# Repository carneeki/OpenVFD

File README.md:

# OpenVFD
Variable Frequency Drive for ATmega328 based Arduinos

A variable frequency drive is a method for controlling AC motors, typically used
in machinery such as a drill press, milling machine or lathe. A VFD typically
permits the use of running 3 phase motors on single phase power, and running
single phase motors on 3 phase power.

The Arduino code presented here will produce 3 PWM signals that approximate sine
waves suitable to drive some transistors that can be used to power AC motors.

EAGLE schematics will later pop up with potential (but untested) circuits that
can be used connect machinery.

VFDs follow several stages, and can be broken up into 3 separate circuits:

1. AC->DC rectification. This means that AC coming in is turned into DC power.
DC power is smoothed out for fewer ripples. This is where 3 phase really shines, there's a lot less ripple.
1. DC->AC inverter. Gnomes receive signals from a controller to turn a bunch of
switches on and off really fast so the motor thinks it sees AC power. Depending
on how fast the gnomes are clicking the switches controls how fast the motor
spins.
1. The controller is the final circuit, which the Arduino code concerns itself
with.

## AC->DC rectification
For single phase circuits, a standard bridge rectifier can be used.
For three phase circuits, a 3 phase rectifier is required (can be made from 6 diodes).

Once DC comes in, a smoothing capacitor (or a bank of them) is required. The
size of the caps depends on the power in and power out.

## DC->AC inverter
The gnomes mentioned are actually MOSFETs, a type of transistor. 6 of them are
hooked up with 3 in parallel from +DC to one leg of each motor. The other three
are connected from each leg of the motor to GND. The gate (or signal receiver)
needs to be hooked up correctly to the controller.

## Inverter Controller
This circuit consists of an Arduino producing three PWM sine waves that go
through a low pass filter. The low pass filter then goes into a device called a comparator. When the sine wave is high, one pin is turned on and goes to the
MOSFET connected to +DC and motor, the other pin is turned off which goes to
the MOSFET connected to the motor and GND.

Certain MOSFETs have trouble remaining on when high voltages are pushed through
them, so it may be necessary to use a controller chip that prevents certain
dangerous conditions, as well as providing an idea of how much juice the motor
is drawing.

## Thanks and references
Much of this code is very very similar to the works found at CPSU and AMAC
below, but with more comments, and designed for use in driving motors.

Omar David Munoz, senior project,
California Polytechnic State University
http://digitalcommons.calpoly.edu/cgi/viewcontent.cgi?article=1129&context=eesp

Martin Nawrath, "Arduino DDS Sine Wave Generator",
Academy of Media Arts Cologne
http://interface.khm.de/index.php/lab/interfaces-advanced/arduino-dds-sinewave-generator/

And the datasheet which is referenced quite a lot in OpenVFD.ino
http://www.atmel.com/images/Atmel-8271-8-bit-AVR-Microcontroller-ATmega48A-48PA-88A-88PA-168A-168PA-328-328P_datasheet_Complete.pdf

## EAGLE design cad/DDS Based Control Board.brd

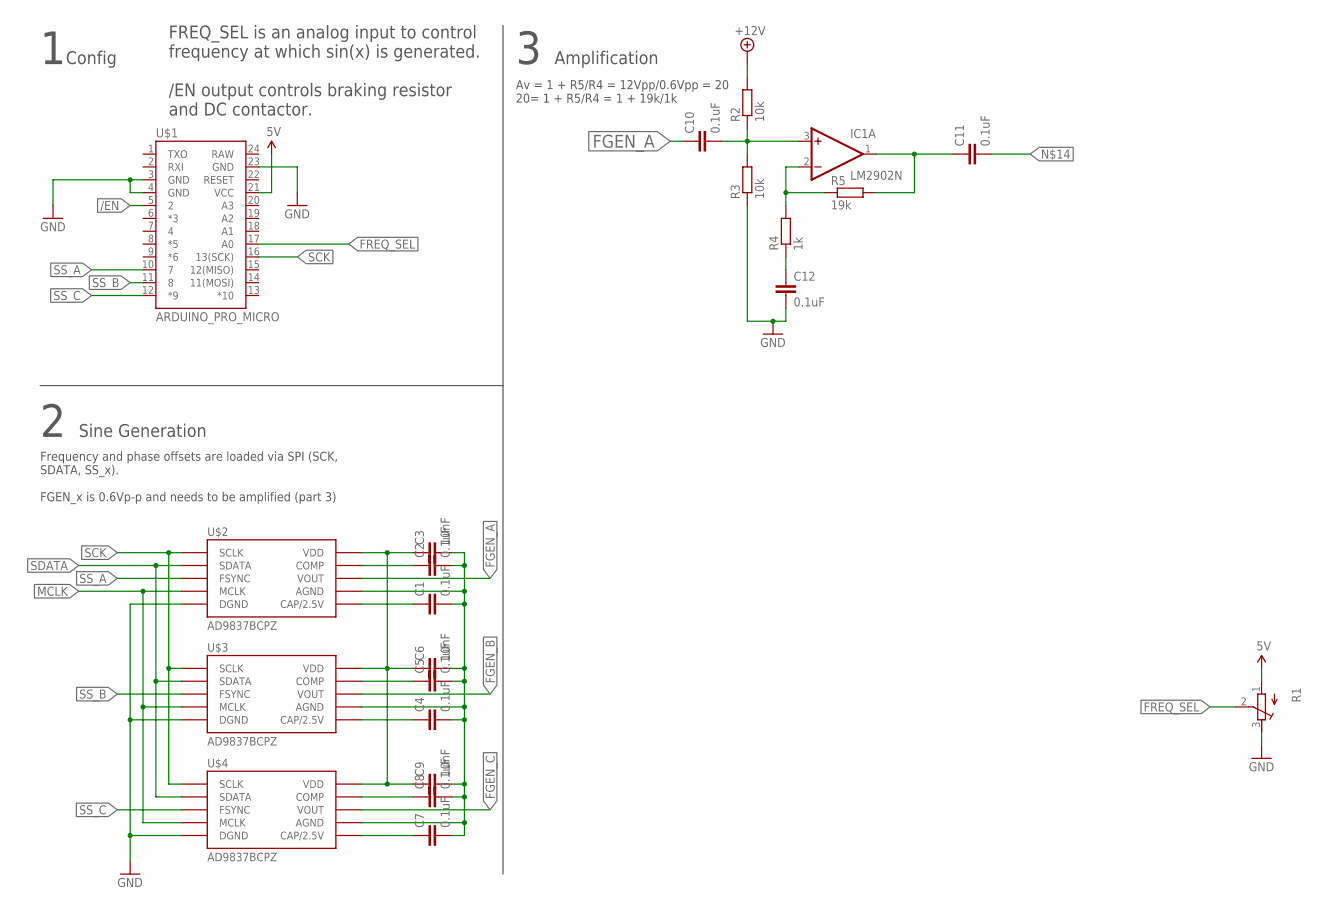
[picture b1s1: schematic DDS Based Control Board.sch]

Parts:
C1, C2, C4, C5, C7, C8, C10, C11, C12: 0.1uF; C025-025X050
C3, C6, C9: 10nF; C025-025X050
IC1: LM2902N; DIL14
R1: R-TRIMM64X; RTRIM64X
R2, R3: 10k; 0207/7
R4: 1k; 0207/7
R5: 19k; 0207/7
U$1: ARDUINO_PRO_MICRO
U$2, U$3, U$4: AD9837BCPZ; AD9837

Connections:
5V: R1.1 (A)
+12V: R2.2
/EN: U$1.5 (2)
FGEN_A: C10.1, U$2.P$10 (VOUT)
FGEN_B: U$3.P$10 (VOUT)
FGEN_C: U$4.P$10 (VOUT)
FREQ_SEL: R1.2 (S), U$1.17 (A0)
GND: C12.2, R1.3 (E), R3.1, U$1.3 (GND), U$1.4 (GND), U$1.23 (GND)
MCLK: U$2.P$5 (MCLK), U$3.P$5 (MCLK), U$4.P$5 (MCLK)
unnamed: C3.1, C6.1, C9.1, U$2.P$2 (VDD), U$3.P$2 (VDD), U$4.P$2 (VDD)
unnamed: C1.2, C2.2, C3.2, C4.2, C5.2, C6.2, C7.2, C8.2, C9.2, U$2.P$9 (AGND), U$3.P$9 (AGND), U$4.P$9 (AGND)
unnamed: C1.1, U$2.P$3 (CAP/2.5V)
unnamed: U$2.P$0 (DGND), U$2.P$4 (DGND), U$3.P$0 (DGND), U$3.P$4 (DGND), U$4.P$0 (DGND), U$4.P$4 (DGND)
unnamed: C2.1, U$2.P$1 (COMP)
unnamed: C5.1, U$3.P$1 (COMP)
unnamed: C8.1, U$4.P$1 (COMP)
unnamed: C7.1, U$4.P$3 (CAP/2.5V)
unnamed: C4.1, U$3.P$3 (CAP/2.5V)
unnamed: C10.2, IC1.3 (+IN), R2.1, R3.2
unnamed: C11.1, IC1.1 (OUT), R5.2
unnamed: IC1.2 (-IN), R4.2, R5.1
unnamed: C12.1, R4.1
SCK: U$1.16 (13(SCK)), U$2.P$7 (SCLK), U$3.P$7 (SCLK), U$4.P$7 (SCLK)
SDATA: U$2.P$6 (SDATA), U$3.P$6 (SDATA), U$4.P$6 (SDATA)
SS_A: U$1.10 (7), U$2.P$8 (FSYNC)
SS_B: U$1.11 (8), U$3.P$8 (FSYNC)
SS_C: U$1.12 (*9), U$4.P$8 (FSYNC)
V+: IC1.4 (V+)
V-: IC1.11 (V-)
VCC: U$1.21 (VCC)

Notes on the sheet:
FREQ_SEL is an analog input to control frequency at which sin(x) is generated. /EN output controls braking resistor and DC contactor.
Frequency and phase offsets are loaded via SPI (SCK, SDATA, SS_x). FGEN_x is 0.6Vp-p and needs to be amplified (part 3)
Config
Sine Generation
Amplification
Av = 1 + R5/R4 = 12Vpp/0.6Vpp = 20 20= 1 + R5/R4 = 1 + 19k/1k

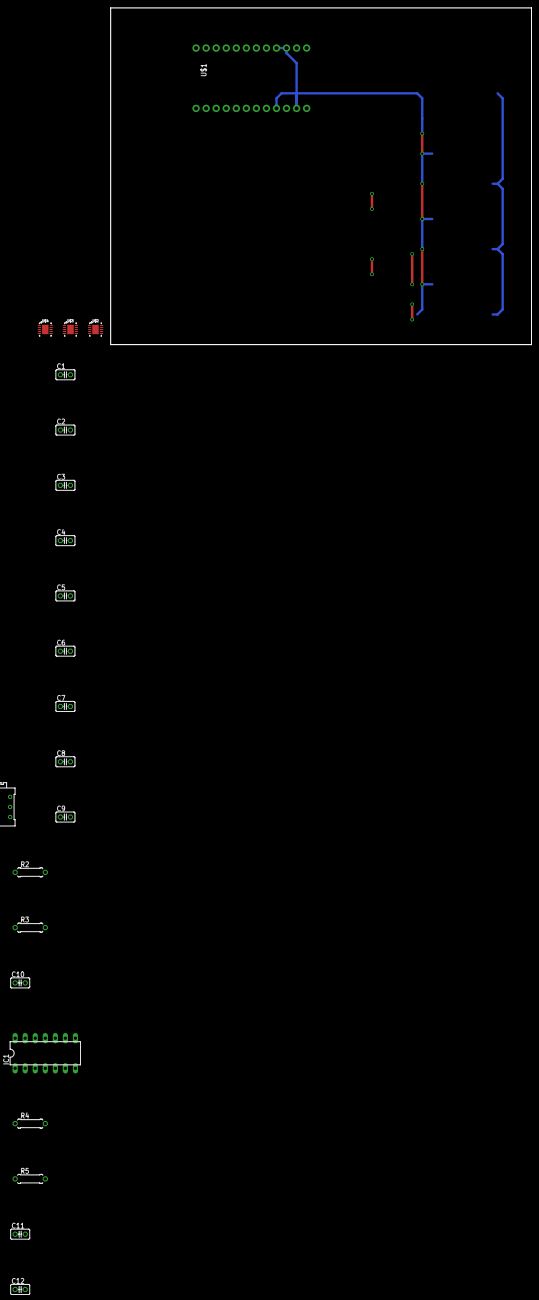
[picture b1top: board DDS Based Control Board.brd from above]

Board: 2 copper layers, 106.3 x 85.1 mm, 22 parts (0 on the bottom side), 22 nets.

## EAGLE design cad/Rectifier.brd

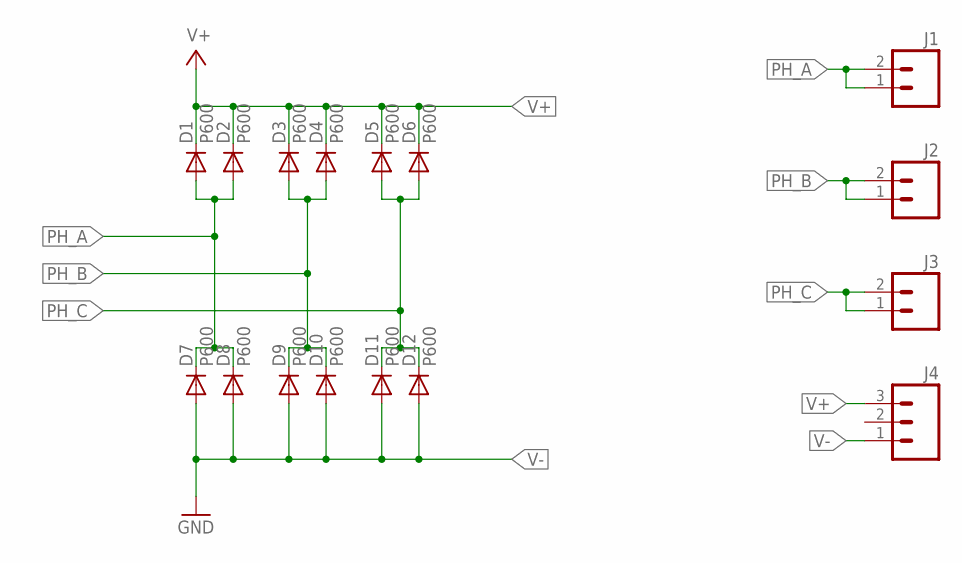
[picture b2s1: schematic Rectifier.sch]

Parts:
D1, D2, D3, D4, D5, D6, D7, D8, D9, D10, D11, D12: P600; P6-15
J1, J2, J3: M025MM; SCREWTERMINAL-5MM-2
J4: M03-SCREW-5MM; SCREWTERMINAL-5MM-3

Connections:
PH_A: D1.A, D2.A, D7.C, D8.C, J1.1, J1.2
PH_B: D3.A, D4.A, D9.C, D10.C, J2.1, J2.2
PH_C: D5.A, D6.A, D11.C, D12.C, J3.1, J3.2
V+: D1.C, D2.C, D3.C, D4.C, D5.C, D6.C, J4.3
V-: D7.A, D8.A, D9.A, D10.A, D11.A, D12.A, J4.1

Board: 2 copper layers, 16 parts (0 on the bottom side), 5 nets, no tracks yet.

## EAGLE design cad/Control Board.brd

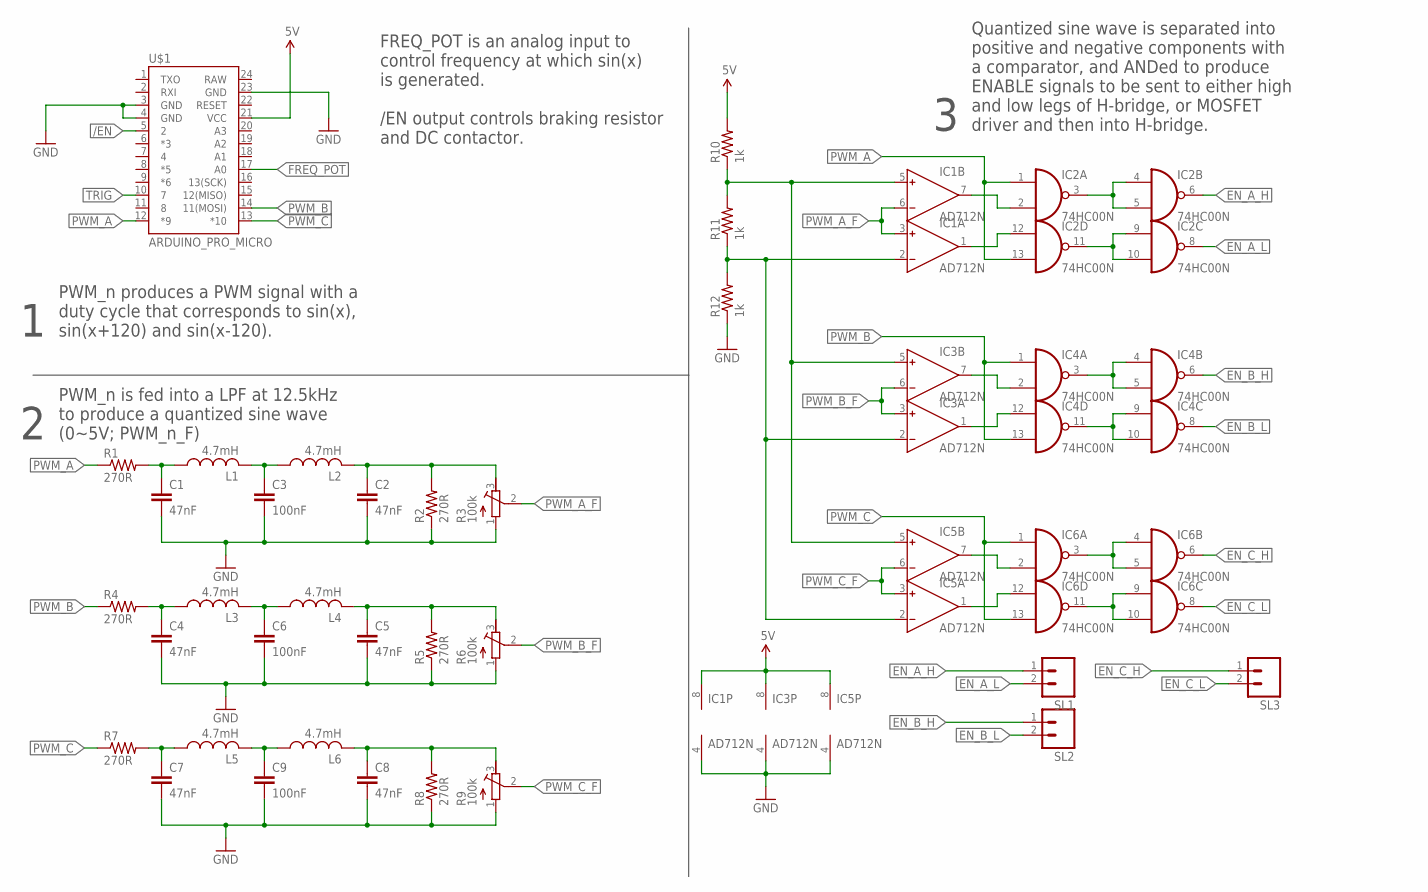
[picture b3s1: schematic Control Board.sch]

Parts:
C1, C2, C4, C5, C7, C8: 47nF; C025-025X050
C3, C6, C9: 100nF; C025-025X050
IC1, IC3, IC5: AD712N; DIL08
IC2, IC4, IC6: 74HC00N; DIL14
L1, L2, L3, L4, L5, L6: 4.7mH; 0207/12
R1, R2, R4, R5, R7, R8: 270R; 0207/7
R3, R6, R9: 100k; RTRIM3296W
R10, R11, R12: 1k; 0207/7
SL1, SL2, SL3: M02PTH; 1X02
U$1: ARDUINO_PRO_MICRO

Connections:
/EN: U$1.5 (2)
EN_A_H: IC2.6 (O), SL1.1
EN_A_L: IC2.8 (O), SL1.2
EN_B_H: IC4.6 (O), SL2.1
EN_B_L: IC4.8 (O), SL2.2
EN_C_H: IC6.6 (O), SL3.1
EN_C_L: IC6.8 (O), SL3.2
FREQ_POT: U$1.17 (A0)
GND: C1.2, C2.2, C3.2, C4.2, C5.2, C6.2, C7.2, C8.2, C9.2, IC1.4 (V-), IC2.7 (GND), IC3.4 (V-), IC4.7 (GND), IC5.4 (V-), IC6.7 (GND), R2.1, R3.1 (A), R5.1, R6.1 (A), R8.1, R9.1 (A), R12.1, U$1.3 (GND), U$1.4 (GND), U$1.23 (GND)
unnamed: C1.1, L1.1, R1.2
unnamed: C3.1, L1.2, L2.1
unnamed: C2.1, L2.2, R2.2, R3.3 (E)
unnamed: C4.1, L3.1, R4.2
unnamed: C6.1, L3.2, L4.1
unnamed: C5.1, L4.2, R5.2, R6.3 (E)
unnamed: C7.1, L5.1, R7.2
unnamed: C9.1, L5.2, L6.1
unnamed: C8.1, L6.2, R8.2, R9.3 (E)
unnamed: IC1.7 (OUT), IC2.2 (I1)
unnamed: IC1.1 (OUT), IC2.12 (I0)
unnamed: IC3.7 (OUT), IC4.2 (I1)
unnamed: IC1.5 (IN+), IC3.5 (IN+), IC5.5 (IN+), R10.1, R11.2
unnamed: IC1.2 (IN-), IC3.2 (IN-), IC5.2 (IN-), R11.1, R12.2
unnamed: IC3.1 (OUT), IC4.12 (I0)
unnamed: IC5.7 (OUT), IC6.2 (I1)
unnamed: IC5.1 (OUT), IC6.12 (I0)
unnamed: IC2.3 (O), IC2.4 (I0), IC2.5 (I1)
unnamed: IC2.9 (I0), IC2.10 (I1), IC2.11 (O)
unnamed: IC4.3 (O), IC4.4 (I0), IC4.5 (I1)
unnamed: IC4.9 (I0), IC4.10 (I1), IC4.11 (O)
unnamed: IC6.9 (I0), IC6.10 (I1), IC6.11 (O)
unnamed: IC6.3 (O), IC6.4 (I0), IC6.5 (I1)
PWM_A: IC2.1 (I0), IC2.13 (I1), R1.1, U$1.12 (*9)
PWM_A_F: IC1.3 (IN+), IC1.6 (IN-), R3.2 (S)
PWM_B: IC4.1 (I0), IC4.13 (I1), R4.1, U$1.14 (11(MOSI))
PWM_B_F: IC3.3 (IN+), IC3.6 (IN-), R6.2 (S)
PWM_C: IC6.1 (I0), IC6.13 (I1), R7.1, U$1.13 (*10)
PWM_C_F: IC5.3 (IN+), IC5.6 (IN-), R9.2 (S)
TRIG: U$1.10 (7)
VCC: IC1.8 (V+), IC2.14 (VCC), IC3.8 (V+), IC4.14 (VCC), IC5.8 (V+), IC6.14 (VCC), R10.2, U$1.21 (VCC)

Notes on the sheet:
FREQ_POT is an analog input to control frequency at which sin(x) is generated. /EN output controls braking resistor and DC contactor.
PWM_n is fed into a LPF at 12.5kHz to produce a quantized sine wave (0~5V; PWM_n_F)
Quantized sine wave is separated into positive and negative components with a comparator, and ANDed to produce ENABLE signals to be sent to either high and low legs of H-bridge, or MOSFET driver and then into H-bridge.
PWM_n produces a PWM signal with a duty cycle that corresponds to sin(x), sin(x+120) and sin(x-120).

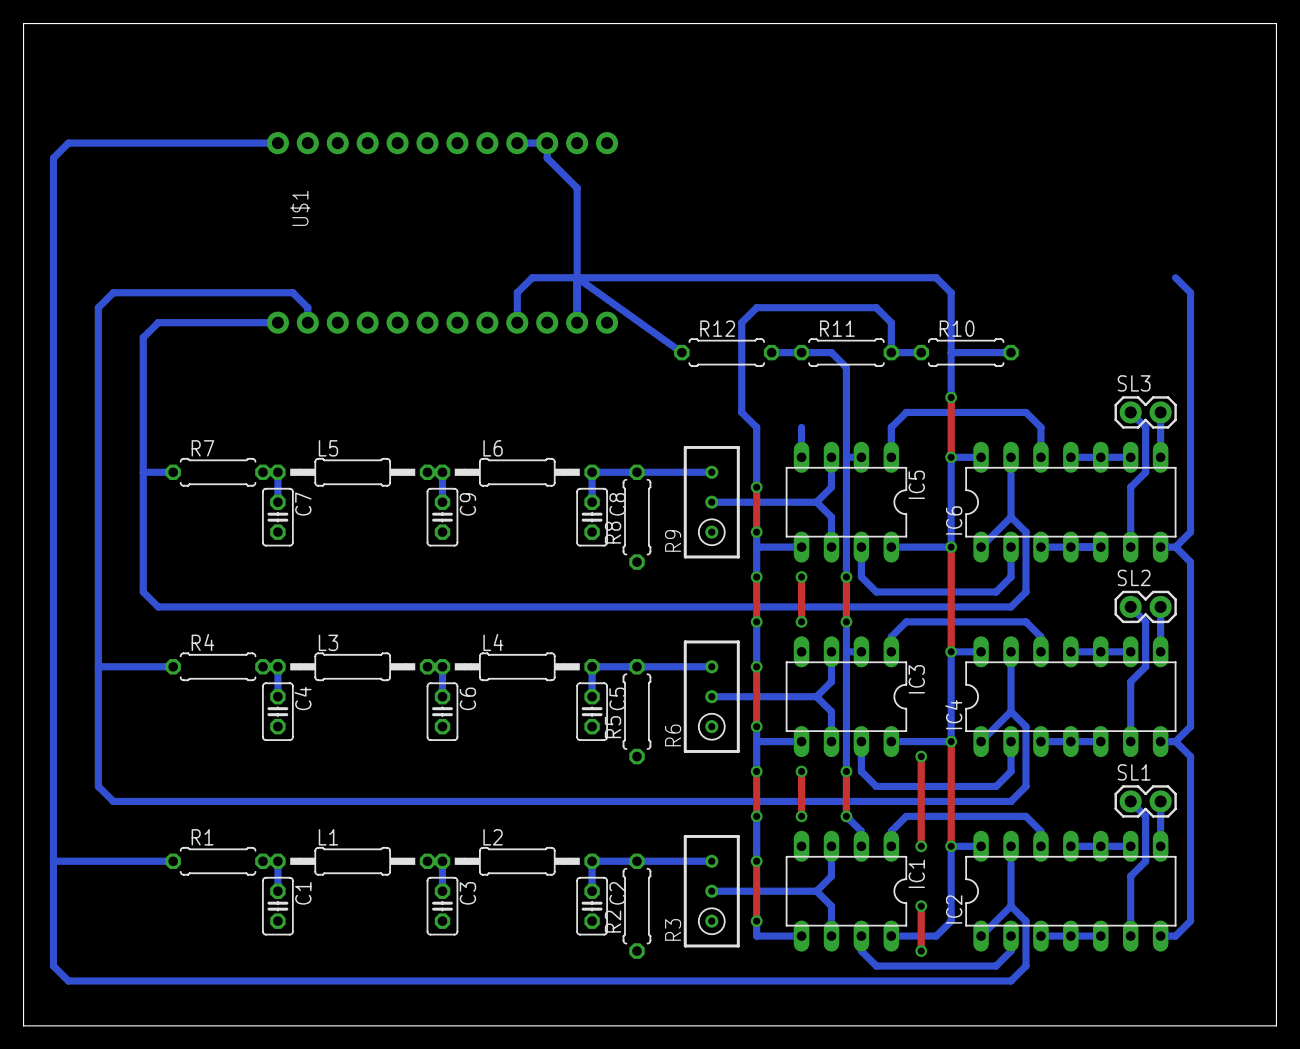
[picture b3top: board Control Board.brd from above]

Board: 2 copper layers, 106.3 x 85.1 mm, 37 parts (0 on the bottom side), 37 nets.

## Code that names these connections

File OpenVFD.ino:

#include "avr/pgmspace.h" // PROGMEM and pgm_read_byte_near()
#include "avr/io.h"

/* Reference clock needs to be measured for the crystal per board (about 16MHz).
 * It is then divided by 510.
 * 16M / 510 = 31372.5490
 */
#define REFCLK 31372.549 // TODO: measure me and adjust

// output frequency
#define FREQ_POT A0  // analog input (A0..A4 are valid) default: A0
#define FREQ_MIN 0   // default: 0
#define FREQ_MAX 100 // default: 100

// pot values might not permit cranking full range so adjust here
#define POT_MIN 0    // default: 0
#define POT_MAX 1023 // default: 1023

// pins for 3 phases: Alpha, Bravo, Charlie, and trigger for CRO.
// ATMega 168 / 328 valid PWM pins are 3,5,6,9,10,11. Non-default values have
// not been tested
#define PWM_A  9     // default:  9
#define PWM_B 10     // default: 10
#define PWM_C 11     // default: 11
#define TRIG   7     // default:  7

/*******************************************************************************
 * Should not need to configure anything below here ***************************/

/*
 * LUT for sin(t) generated (by spreadsheet) using this formula:
 * x = ROUND( (255/2) * (1+SIN((2*PI()) * (t/256))) )
 *
 * where 0 <= t <= 255 ; keeping one period of sine in nvram
 *
 * Keeping LUT is way faster than calculating all the time
 */
const byte sin256[] PROGMEM =
{
//  0   1   2   3   4   5   6   7   8   9   a   b   c   d   e   f
  128,131,134,137,140,143,146,149,152,155,158,162,165,167,170,173, // 00:0f
  176,179,182,185,188,190,193,196,198,201,203,206,208,211,213,215, // 10:1f
  218,220,222,224,226,228,230,232,234,235,237,238,240,241,243,244, // 20:2f
  245,246,248,249,250,250,251,252,253,253,254,254,254,255,255,255, // 30:3f
  255,255,255,255,254,254,254,253,253,252,251,250,250,249,248,246, // 40:4f
  245,244,243,241,240,238,237,235,234,232,230,228,226,224,222,220, // 50:5f
  218,215,213,211,208,206,203,201,198,196,193,190,188,185,182,179, // 60:6f
  176,173,170,167,165,162,158,155,152,149,146,143,140,137,134,131, // 70:7f
  128,124,121,118,115,112,109,106,103,100, 97, 93, 90, 88, 85, 82, // 80:8f
   79, 76, 73, 70, 67, 65, 62, 59, 57, 54, 52, 49, 47, 44, 42, 40, // 90:9f
   37, 35, 33, 31, 29, 27, 25, 23, 21, 20, 18, 17, 15, 14, 12, 11, // a0:af
   10,  9,  7,  6,  5,  5,  4,  3,  2,  2,  1,  1,  1,  0,  0,  0, // b0:bf
    0,  0,  0,  0,  1,  1,  1,  2,  2,  3,  4,  5,  5,  6,  7,  9, // c0:cf
   10, 11, 12, 14, 15, 17, 18, 20, 21, 23, 25, 27, 29, 31, 33, 35, // d0:df
   37, 40, 42, 44, 47, 49, 52, 54, 57, 59, 62, 65, 67, 70, 73, 76, // e0:ef
   79, 82, 85, 88, 90, 93, 97,100,103,106,109,112,115,118,121,124  // f0:ff
};

// phase offsets (n * 255 / 3)
#define A_OFFSET 0   // (0x00)
#define B_OFFSET 85  // (0x55)
#define C_OFFSET 170 // (0xaa)

int freq; // output frequency
const double TUN_K=( 4294967296.0 / REFCLK ); // tuning coefficient

// variables in ISR
volatile byte icnt;            //
volatile byte icnt1;           //
volatile byte c4ms;            // counter incremented every 4ms
volatile unsigned long phaccu; // phase accumulator
volatile unsigned long tune;   // dds tuning word

void setup()
{
  pinMode(PWM_A, OUTPUT);
  pinMode(PWM_B, OUTPUT);
  pinMode(PWM_C, OUTPUT);
  pinMode(TRIG, OUTPUT);

  setup_timers(); // this also disables interrupts
}

void loop()
{
  if(c4ms > 250)
  {
    c4ms = 0;
    freq = map(analogRead(FREQ_POT), POT_MIN, POT_MAX, FREQ_MIN, FREQ_MAX);

    TIMSK2 &= ~(_BV(TOIE2)); // disable Timer2 interrupt
    tune = TUN_K*freq;       // update DDS tuning word
    TIMSK2 |= _BV(TOIE2);    // re-enable Timer2 interrupt
  }
}


/**
 * Set prescaler to 1, PWM mode to phase correct PWM
 * @see https://www.arduino.cc/en/Tutorial/SecretsOfArduinoPWM
 * @see http://www.atmel.com/images/Atmel-8271-8-bit-AVR-Microcontroller-ATmega48A-48PA-88A-88PA-168A-168PA-328-328P_datasheet_Complete.pdf
 * @see datasheet section 15.7.4 "Phase Correct PWM Mode"
 */
void setup_timers()
{
  /* Timer Registers:
   * n = timer n (0,1,2)
   * x = bit X
   * each timer has slightly different config bits, datasheet section 9, 15, 18
   *
   * TCCRnA = Timer/Counter Control Register A
   * TCCRnB = Timer/Counter Control Register B
   * TCCRxx holds the main control bits for the timer
   *
   * CS = Clock Select bits for prescaler (datasheet 9.12.2)
   *
   * COMnA = Comparator Output A
   * COMnB = Comparator Output B
   * Comparator sets levels at which outputs A and B are affected
   */

   /* Disable Timer 0 so it cannot interrupt the loop
    * See Section 15.9.6 */
   TIMSK0 &= ~(_BV(TOIE0));

   /* Enable Timer 1
    * See Section 16.11.8 */
   TIMSK1 |= _BV(TOIE1);

   /* Enable Timer 2
    * See Section 18.11.6 */
   TIMSK2 |= _BV(TOIE2);

  /*** Timer 1 ***/
  /* Timer 1 Clock Prescaler to no prescaling (CS12:0 = 001)
   * Section 16.11.2 Table 16-5 */
  TCCR1B &= ~(_BV(CS12));
  TCCR1B &= ~(_BV(CS11));
  TCCR1B |= _BV(CS10);

  /* Timer 1 Set WGM to Phase Correct PWM 8 bit (WGM13:0 = 0001)
   * Section 16.11.1, Table 16-4 */
  TCCR1B &= ~(_BV(WGM13));
  TCCR1B &= ~(_BV(WGM12));
  TCCR1B &= ~(_BV(WGM11));
  TCCR1B |= _BV(WGM10);

  /* Timer 1 Set Compare Output Mode (COM1A1:0 = COM1B1:0 = 01)
   * Section 16.11.1, Table 16-2 */
  TCCR1A |= _BV(COM1A1);    // Clear OC1A on compare match -- and --
  TCCR1A &= ~(_BV(COM1A0)); // Set OC1A at bottom
  TCCR1A |= _BV(COM1B1);    // Clear OC1B on compare match -- and --
  TCCR1A &= ~(_BV(COM1A0)); // Set OC1B at bottom

  /*** Timer 2 ***/
  /* Timer 2 Clock Prescaler to no prescaling (CS22:0 = 001)
   * Section 18.11.2 */
  TCCR2B &= ~(_BV(CS22));
  TCCR2B &= ~(_BV(CS21));
  TCCR2B |= _BV(CS20);

  /* Timer2 Set WGM to Phase Correct PWM (WGM22:0 = 001)
   * Section 18.7.4 */
  TCCR2B &= ~(_BV(WGM22));
  TCCR2B &= ~(_BV(WGM22));
  TCCR2A |= _BV(WGM20);

  /* Timer 2 Set compare output mode (COM2A1:0 = 01)
   * Section 18.11.1 */
  TCCR2A |= _BV(COM2A1);    // Clear OC2A on Compare Match when up count -- and
  TCCR2A &= ~(_BV(COM2A0)); // Set OC2A on Compare Match when down count.

  // Timer 2 NOTE: we can leave FOC2B:A unset also, bits 4 and 5 are reserved
}


/**
 * Timer 2 interrupt - 31.25kHz ~= 32us
 * Fout = (tuning word * REFCLK) / 2^32
 * Runtime: 8us (incl stack push + pop)
 */
ISR(TIMER2_OVF_vect)
{
  PORTD |= _BV(TRIG);  // Trigger CRO
  phaccu += tune;      // soft DDS, phase accu with 32 bits
  icnt = phaccu >> 24; // use upper 8 bits for phase accu as frequency information

  // read byte from sin256 table using the phase offset as the address
  // place into output compar registers
  OCR2A = pgm_read_byte_near(sin256 + (uint8_t)(icnt + A_OFFSET));
  OCR1A = pgm_read_byte_near(sin256 + (uint8_t)(icnt + B_OFFSET));
  OCR1B = pgm_read_byte_near(sin256 + (uint8_t)(icnt + C_OFFSET));

  if (icnt1++ == 125) // increment variable c4ms every 4 milliseconds
  {
    c4ms++;
    icnt1 = 0;
  }
  PORTD &= ~(_BV(TRIG)); // Reset CRO trigger
}

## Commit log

2016-08-23 initial commit and import of license
    initial code commit.
    license from https://raw.githubusercontent.com/idleberg/Creative-Commons-Markdown/spaces/legacy/3.0/by-nc-sa.markdown
2016-08-23 added more useful stuff to readme, including references
2016-08-23 fix up numbering
2016-08-23 add reference to datasheet
2017-04-13 made sin256[] more accurate
2017-04-14 fixed OBO problem that caused compiler warnings (and incorrect data) also tidied the LUT and corrected the formula for spreadsheet generation
2017-04-14 typo
2018-04-01 add cad files, move arduino source to folder. this cad has not been looked at in over a year and a bit, it may not work. it may set things on fire. do not use!

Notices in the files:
parts and their libraries:
SparkFun-Boards: Licensing: Creative Commons ShareAlike 4.0 International - https://creativecommons.org/licenses/by-sa/4.0
